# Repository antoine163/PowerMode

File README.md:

# PowerMod
Module d’alimentation compatible avec les breadboard  
**Note**: Des valeurs de composants restent à finaliser...

## mod_boost_ap3012
Entrée (J1, J2): 5V  
Sortie boost (J3, J4): 24V

## mod_buck_bd95835efj
Entrée (J1, J2, J6): 12V / 1.5A  
Sortie buck (J4): 5.6V / 2A  
Sortie ldo (J7, J5): 5V / 1.2A  

**Attention:** Le courant max sur l'ensemble des sortie est de 3A.

## mod_buck_xc9263
Entrée (J1, J2, J7): 12V  
Sortie 1 buck (J4): 5.35V  
Sortie 1 ldo (J5, J6): 5V / 200mA  
Sortie 2 buck (J8): 3.5V  
Sortie 2 ldo (J5, J6): 3.3V / 250mA  
Sortie 3 buck (J9): 2.1V  
Sortie 3 ldo (J5, J6): 1.8V / 200mA  

# Models 3D
Certains modèles 3D ne sont pas inclus dans ce projet. Il vous faudra les télécharger sur le site des fabricants si vous en avez besoin.

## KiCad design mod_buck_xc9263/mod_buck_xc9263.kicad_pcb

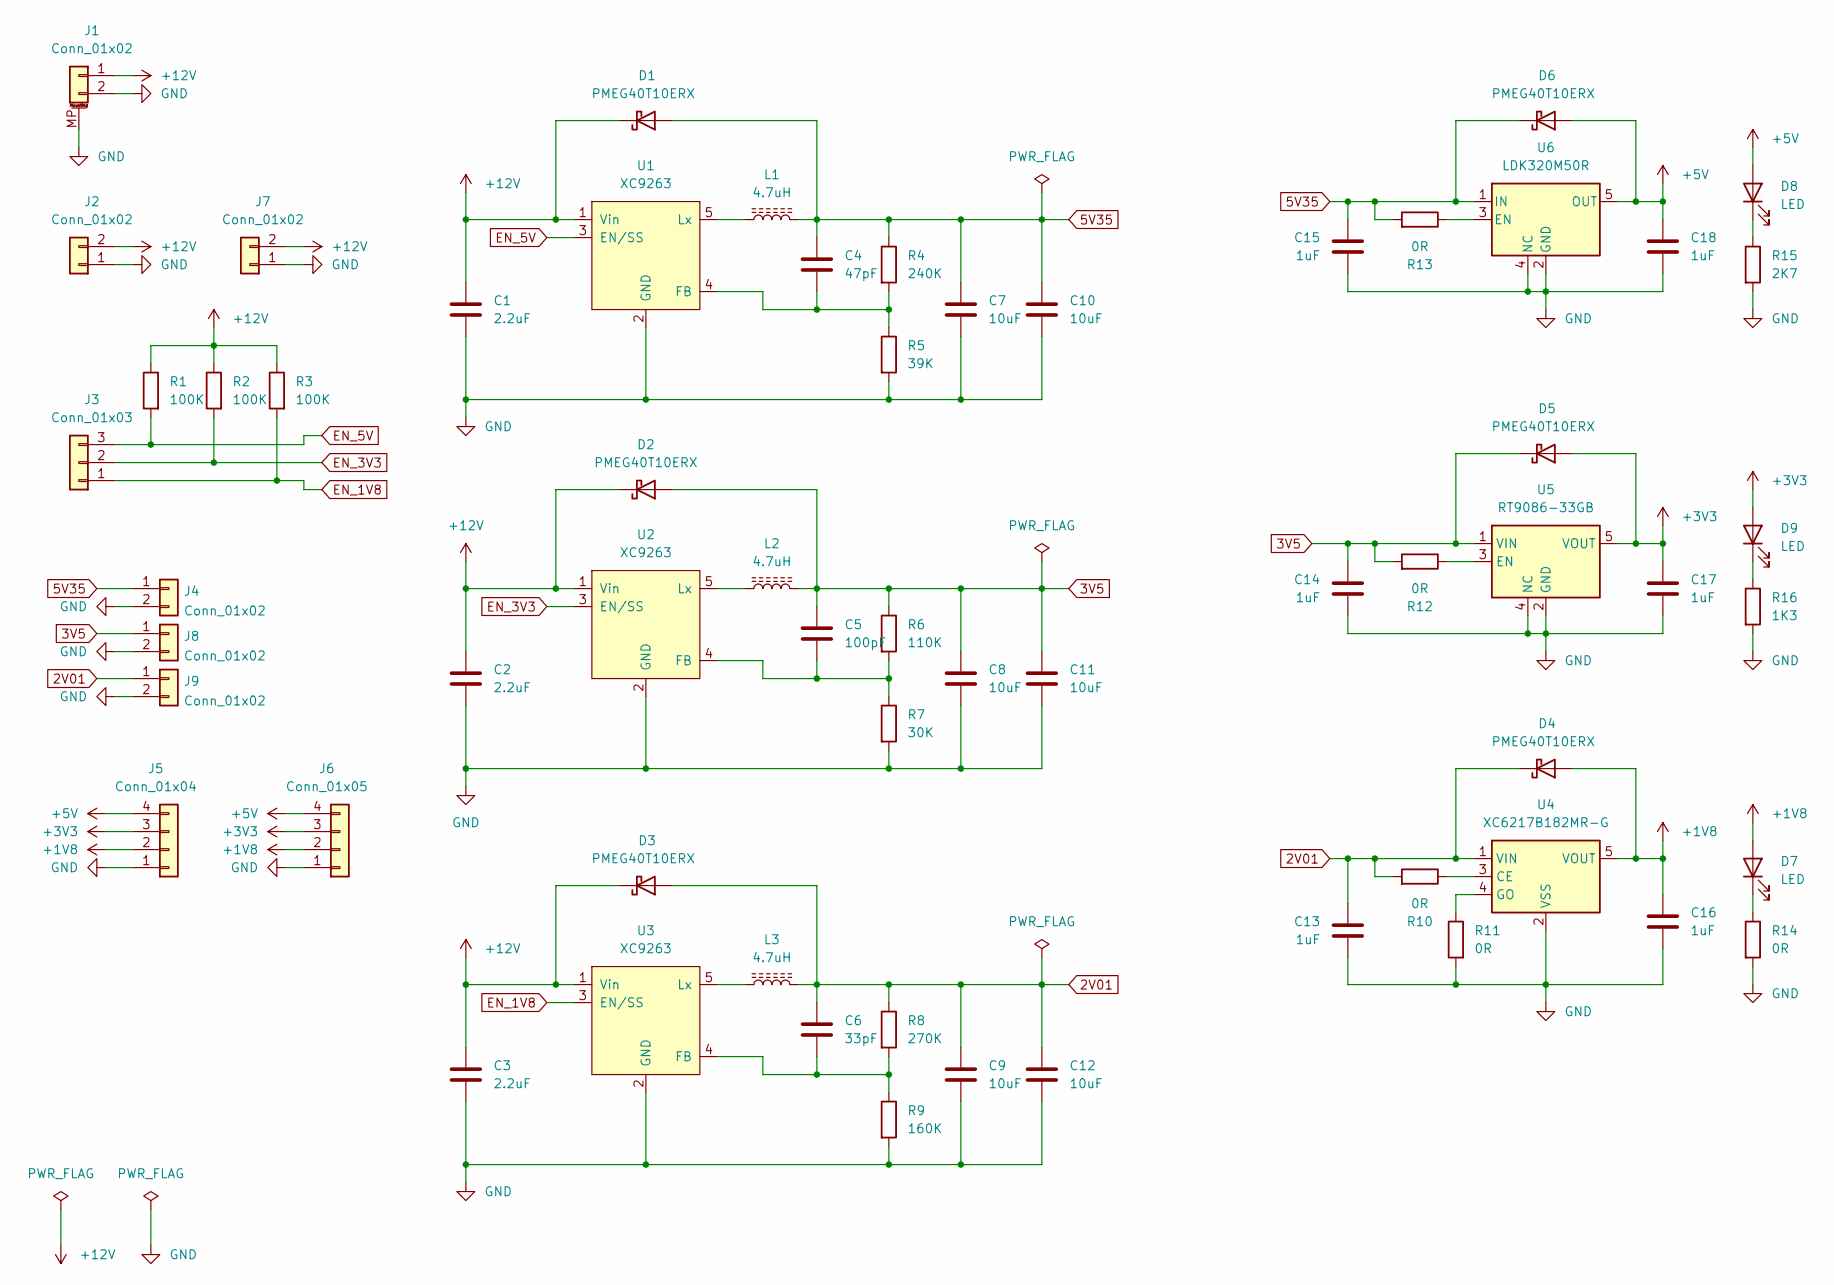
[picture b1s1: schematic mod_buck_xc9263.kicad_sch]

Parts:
C1, C2, C3: 2.2uF; C_0603_1608Metric_Pad1.08x0.95mm_HandSolder
C4: 47pF; C_0402_1005Metric_Pad0.74x0.62mm_HandSolder
C5: 100pF; C_0402_1005Metric_Pad0.74x0.62mm_HandSolder
C6: 33pF; C_0402_1005Metric_Pad0.74x0.62mm_HandSolder
C7, C8, C9, C10, C11, C12: 10uF; C_0805_2012Metric_Pad1.18x1.45mm_HandSolder
C13, C14, C15, C16, C17, C18: 1uF; C_0603_1608Metric_Pad1.08x0.95mm_HandSolder
D1, D2, D3, D4, D5, D6: PMEG40T10ERX; Nexperia_CFP3_SOD-123W
D7, D8, D9: LED; LED_0603_1608Metric_Pad1.05x0.95mm_HandSolder
J1: Conn_01x02; JST_PH_S2B-PH-SM4-TB_1x02-1MP_P2.00mm_Horizontal
J2, J7: Conn_01x02; PinHeader_1x02_P2.54mm_Vertical
J3: Conn_01x03; PinHeader_1x03_P2.54mm_Vertical
J4, J8, J9: Conn_01x02; JST_PH_B2B-PH-K_1x02_P2.00mm_Vertical
J5: Conn_01x04; JST_PH_B4B-PH-K_1x04_P2.00mm_Vertical
J6: Conn_01x05; PinHeader_1x04_P2.54mm_Vertical
L1, L2, L3: 4.7uH; L_TDK_VLS252012HBX_Handsoldering
R1, R2, R3: 100K; R_0402_1005Metric_Pad0.72x0.64mm_HandSolder
R4: 240K; R_0402_1005Metric_Pad0.72x0.64mm_HandSolder
R5: 39K; R_0402_1005Metric_Pad0.72x0.64mm_HandSolder
R6: 110K; R_0402_1005Metric_Pad0.72x0.64mm_HandSolder
R7: 30K; R_0402_1005Metric_Pad0.72x0.64mm_HandSolder
R8: 270K; R_0402_1005Metric_Pad0.72x0.64mm_HandSolder
R9: 160K; R_0402_1005Metric_Pad0.72x0.64mm_HandSolder
R10, R11, R12, R13, R14: 0R; R_0402_1005Metric_Pad0.72x0.64mm_HandSolder
R15: 2K7; R_0402_1005Metric_Pad0.72x0.64mm_HandSolder
R16: 1K3; R_0402_1005Metric_Pad0.72x0.64mm_HandSolder
U1, U2, U3: XC9263; SOT-23-5
U4: XC6217B182MR-G; SOT-23-5
U5: RT9086-33GB; SOT-23-5
U6: LDK320M50R; SOT-23-5

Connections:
2V01: C6.1, C9.1, C12.1, C13.2, D3.2 (A), D4.1 (K), J9.1, L3.2, R8.1, R10.2, U4.1 (VIN)
3V5: C5.1, C8.1, C11.1, C14.2, D2.2 (A), D5.1 (K), J8.1, L2.2, R6.1, R12.2, U5.1 (VIN)
5V35: C4.1, C7.1, C10.1, C15.2, D1.2 (A), D6.1 (K), J4.1, L1.2, R4.1, R13.2, U6.1 (IN)
+1V8: C16.1, D4.2 (A), D7.2 (A), J5.2, J6.2, U4.5 (VOUT)
+3V3: C17.1, D5.2 (A), D9.2 (A), J5.3, J6.3, U5.5 (VOUT)
+5V: C18.1, D6.2 (A), D8.2 (A), J5.4, J6.4, U6.5 (OUT)
+12V: C1.1, C2.1, C3.1, D1.1 (K), D2.1 (K), D3.1 (K), J1.1, J2.2, J7.2, R1.1, R2.1, R3.1, U1.1 (Vin), U2.1 (Vin), U3.1 (Vin)
EN_1V8: J3.1, R3.2, U3.3 (EN/SS)
EN_3V3: J3.2, R2.2, U2.3 (EN/SS)
EN_5V: J3.3, R1.2, U1.3 (EN/SS)
GND: C1.2, C2.2, C3.2, C7.2, C8.2, C9.2, C10.2, C11.2, C12.2, C13.1, C14.1, C15.1, C16.2, C17.2, C18.2, J1.2, J1.MP (MountPin), J2.1, J4.2, J5.1, J6.1, J7.1, J8.2, J9.2, R5.2, R7.2, R9.2, R11.2, R14.2, R15.2, R16.2, U1.2 (GND), U2.2 (GND), U3.2 (GND), U4.2 (VSS), U5.2 (GND), U5.4 (NC), U6.2 (GND), U6.4 (NC)
unnamed: C4.2, R4.2, R5.1, U1.4 (FB)
unnamed: C5.2, R6.2, R7.1, U2.4 (FB)
unnamed: C6.2, R8.2, R9.1, U3.4 (FB)
unnamed: D7.1 (K), R14.1
unnamed: D8.1 (K), R15.1
unnamed: D9.1 (K), R16.1
unnamed: L1.1, U1.5 (Lx)
unnamed: L2.1, U2.5 (Lx)
unnamed: L3.1, U3.5 (Lx)
unnamed: R10.1, U4.3 (CE)
unnamed: R11.1, U4.4 (GO)
unnamed: R12.1, U5.3 (EN)
unnamed: R13.1, U6.3 (EN)

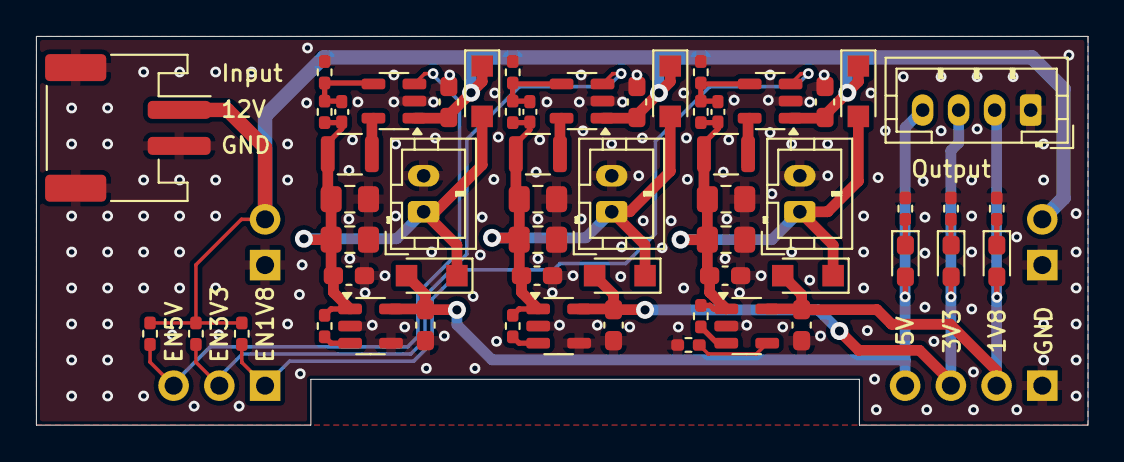
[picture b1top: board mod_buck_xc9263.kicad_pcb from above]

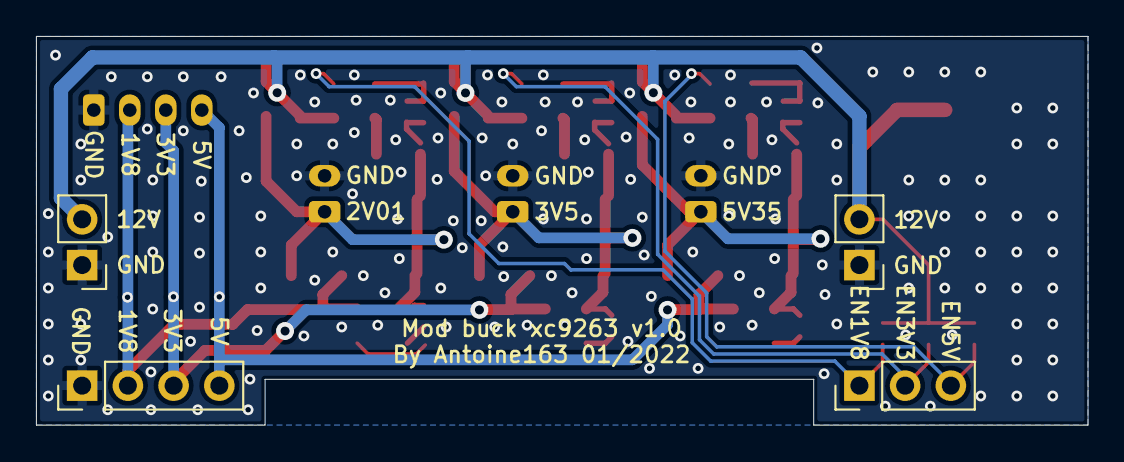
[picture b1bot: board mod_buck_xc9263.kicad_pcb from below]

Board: 2 copper layers, 58.4 x 21.6 mm, 61 parts (4 on the bottom side), 24 nets.

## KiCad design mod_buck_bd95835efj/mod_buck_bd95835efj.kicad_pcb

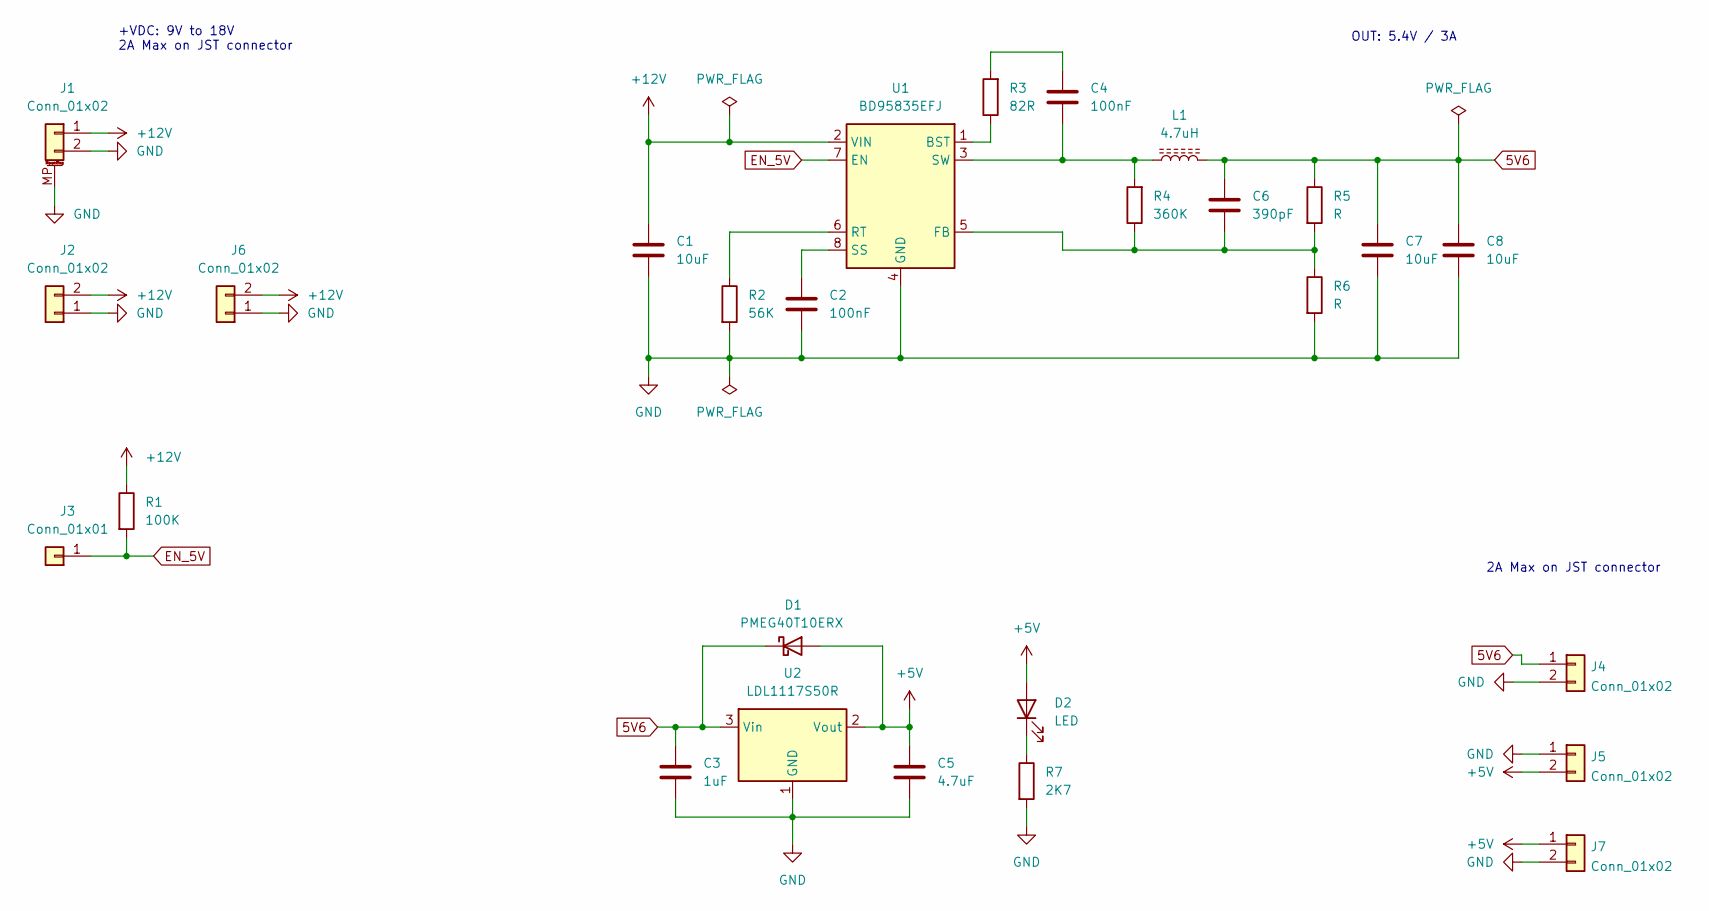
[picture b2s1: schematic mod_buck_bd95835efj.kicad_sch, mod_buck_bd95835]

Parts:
C1, C7, C8: 10uF; C_0805_2012Metric_Pad1.18x1.45mm_HandSolder
C2, C4: 100nF; C_0402_1005Metric_Pad0.74x0.62mm_HandSolder
C3: 1uF; C_0603_1608Metric_Pad1.08x0.95mm_HandSolder
C5: 4.7uF; C_0805_2012Metric_Pad1.18x1.45mm_HandSolder
C6: 390pF; C_0402_1005Metric_Pad0.74x0.62mm_HandSolder
D1: PMEG40T10ERX; Nexperia_CFP3_SOD-123W
D2: LED; LED_0603_1608Metric_Pad1.05x0.95mm_HandSolder
J1: Conn_01x02; JST_PH_S2B-PH-SM4-TB_1x02-1MP_P2.00mm_Horizontal
J2, J5, J6: Conn_01x02; PinHeader_1x02_P2.54mm_Vertical
J3: Conn_01x01; PinHeader_1x01_P2.54mm_Vertical
J4, J7: Conn_01x02; JST_PH_B2B-PH-K_1x02_P2.00mm_Vertical
L1: 4.7uH; L_TDK_VLS6045AF_Handsoldering
R1: 100K; R_0402_1005Metric_Pad0.72x0.64mm_HandSolder
R2: 56K; R_0402_1005Metric_Pad0.72x0.64mm_HandSolder
R3: 82R; R_0402_1005Metric_Pad0.72x0.64mm_HandSolder
R4: 360K; R_0402_1005Metric_Pad0.72x0.64mm_HandSolder
R5, R6: R; R_0402_1005Metric_Pad0.72x0.64mm_HandSolder
R7: 2K7; R_0402_1005Metric_Pad0.72x0.64mm_HandSolder
U1: BD95835EFJ; HTSOP-8-1EP_3.9x4.9mm_P1.27mm_EP2.4x3.2mm_ThermalVias
U2: LDL1117S50R; SOT-223-3_TabPin2

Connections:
5V6: C3.1, C6.1, C7.1, C8.1, D1.1 (K), J4.1, L1.2, R5.1, U2.3 (Vin)
+5V: C5.1, D1.2 (A), D2.2 (A), J5.2, J7.1, U2.2 (Vout)
+12V: C1.1, J1.1, J2.2, J6.2, R1.1, U1.2 (VIN)
EN_5V: J3.1, R1.2, U1.7 (EN)
GND: C1.2, C2.2, C3.2, C5.2, C7.2, C8.2, J1.2, J1.MP (MountPin), J2.1, J4.2, J5.1, J6.1, J7.2, R2.2, R6.2, R7.2, U1.4 (GND), U1.9 (GND), U2.1 (GND)
unnamed: C2.1, U1.8 (SS)
unnamed: C4.1, R3.2
unnamed: C4.2, L1.1, R4.2, U1.3 (SW)
unnamed: C6.2, R4.1, R5.2, R6.1, U1.5 (FB)
unnamed: D2.1 (K), R7.1
unnamed: R2.1, U1.6 (RT)
unnamed: R3.1, U1.1 (BST)

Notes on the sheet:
OUT: 5.4V / 3A
2A Max on JST connector
+VDC: 9V to 18V 2A Max on JST connector

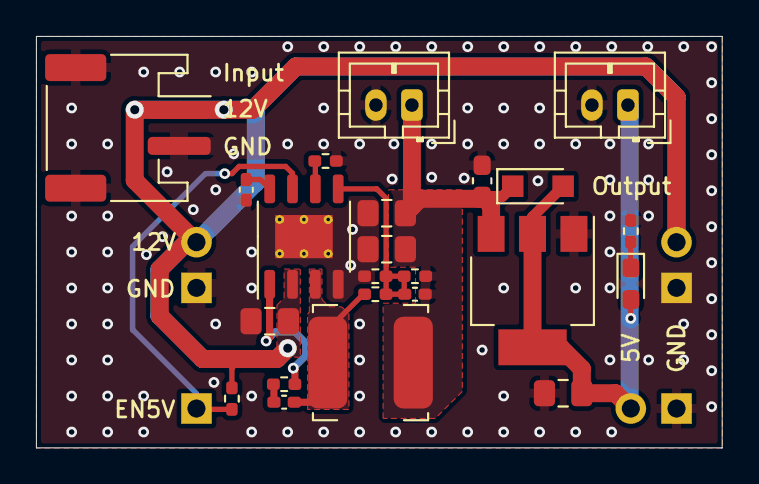
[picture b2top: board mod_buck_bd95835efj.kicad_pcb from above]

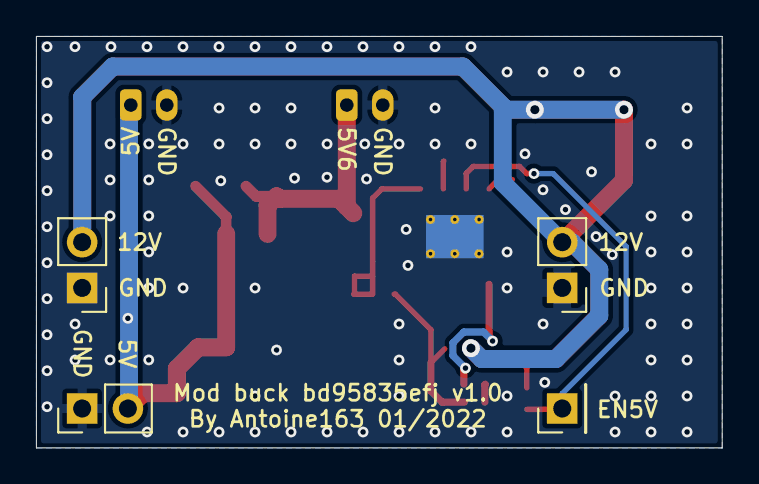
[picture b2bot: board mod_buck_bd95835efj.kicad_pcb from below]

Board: 2 copper layers, 38.1 x 22.9 mm, 27 parts (4 on the bottom side), 12 nets.

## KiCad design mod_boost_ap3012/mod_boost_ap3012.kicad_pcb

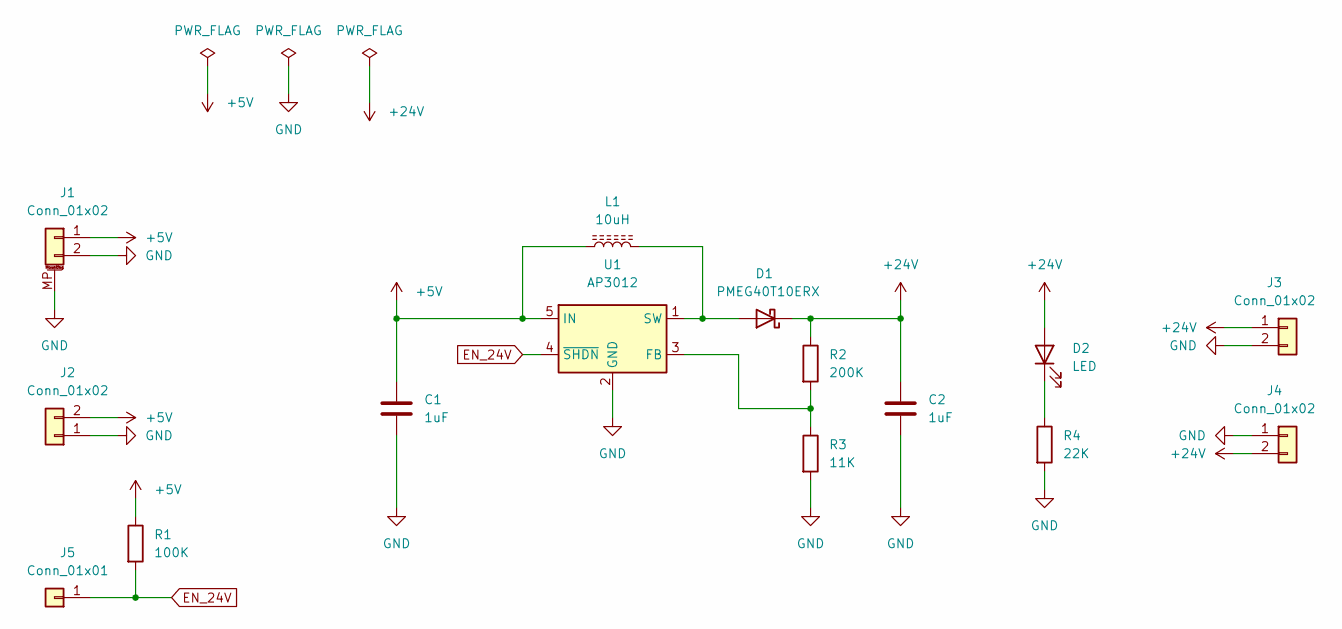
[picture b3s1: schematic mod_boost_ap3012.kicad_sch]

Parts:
C1, C2: 1uF; C_0603_1608Metric_Pad1.08x0.95mm_HandSolder
D1: PMEG40T10ERX; Nexperia_CFP3_SOD-123W
D2: LED; LED_0603_1608Metric_Pad1.05x0.95mm_HandSolder
J1: Conn_01x02; JST_PH_S2B-PH-SM4-TB_1x02-1MP_P2.00mm_Horizontal
J2, J4: Conn_01x02; PinHeader_1x02_P2.54mm_Vertical
J3: Conn_01x02; JST_PH_B2B-PH-K_1x02_P2.00mm_Vertical
J5: Conn_01x01; PinHeader_1x01_P2.54mm_Vertical
L1: 10uH; L_TDK_VLS252012HBX_Handsoldering
R1: 100K; R_0402_1005Metric_Pad0.72x0.64mm_HandSolder
R2: 200K; R_0402_1005Metric_Pad0.72x0.64mm_HandSolder
R3: 11K; R_0402_1005Metric_Pad0.72x0.64mm_HandSolder
R4: 22K; R_0402_1005Metric_Pad0.72x0.64mm_HandSolder
U1: AP3012; SOT-23-5

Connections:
+5V: C1.1, J1.1, J2.2, L1.1, R1.1, U1.5 (IN)
+24V: C2.1, D1.1 (K), D2.2 (A), J3.1, J4.2, R2.1
EN_24V: J5.1, R1.2, U1.4 (~SHDN)
GND: C1.2, C2.2, J1.2, J1.MP (MountPin), J2.1, J3.2, J4.1, R3.2, R4.2, U1.2 (GND)
unnamed: D1.2 (A), L1.2, U1.1 (SW)
unnamed: D2.1 (K), R4.1
unnamed: R2.2, R3.1, U1.3 (FB)

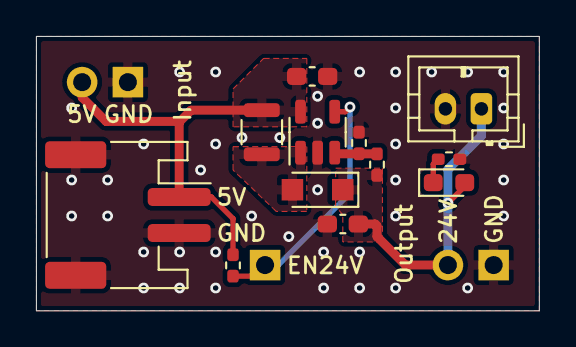
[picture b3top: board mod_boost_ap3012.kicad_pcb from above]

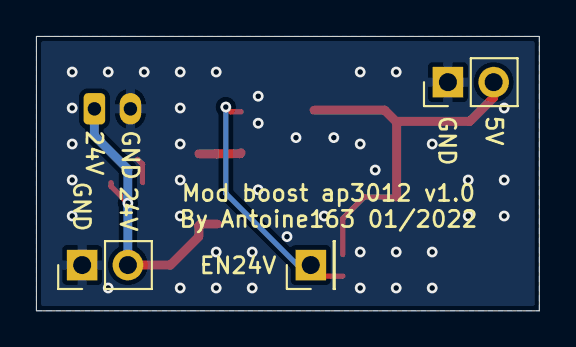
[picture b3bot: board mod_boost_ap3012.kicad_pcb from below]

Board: 2 copper layers, 27.9 x 15.2 mm, 15 parts (3 on the bottom side), 7 nets.

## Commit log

2022-01-08 Ajout des fichiers kicad
2022-01-08 Mise à jour du readme et ajour des visuels
2022-01-08 Ajout des fichiers png
2022-01-27 Ajout photo de la carte Mod_buck_xc9263
2024-03-16 Correction readme
2024-03-16 Suppression des models 3D
2024-03-16 suppression de maxima-circuits
2024-03-16 ajout maxima-circuits en submodule
2024-03-17 update 3d inductor
